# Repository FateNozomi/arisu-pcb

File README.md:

# Arisu Keyboard PCB
アリス PCB designed using KiCad. The layout is inspired by Lyn's EM7 and TGR Alice with some modification of my own.

Key differences:
- I removed the extra [B] key on the right half and shifted the [NM,.?] row to the left by 0.25U.
- Shifted the 3 keys to the right and added arrow keys.
- Tweaked the bottom so that the 1.5U keys doesn't protrude out a little.

Shifting the [NM,.?] row to the left by 0.25U required quite some work on the arrangement of keys for the right half.
As a result, this does not give the same typing experience as Lyn's EM7 and TGR Alice.
Lyn's EM7 and TGR Alice uses the home row as the center point to vertically align both halves while I used the number row instead.
Due to the nature of staggered keyboards, aligning using the number row resulted in the home row not being aligned.

Disclaimer: Use these files at your own risk.

## Gerber Files
Download the gerber files under [releases](https://github.com/FateNozomi/arisu-pcb/releases).

## Assembly
For the components required, you may refer to the bill of materials included along with the release as reference or load up the design file in KiCad.
All the components can be soldered using a regular soldering iron, though soldering the Micro USB receptacle might be the biggest hurdle.

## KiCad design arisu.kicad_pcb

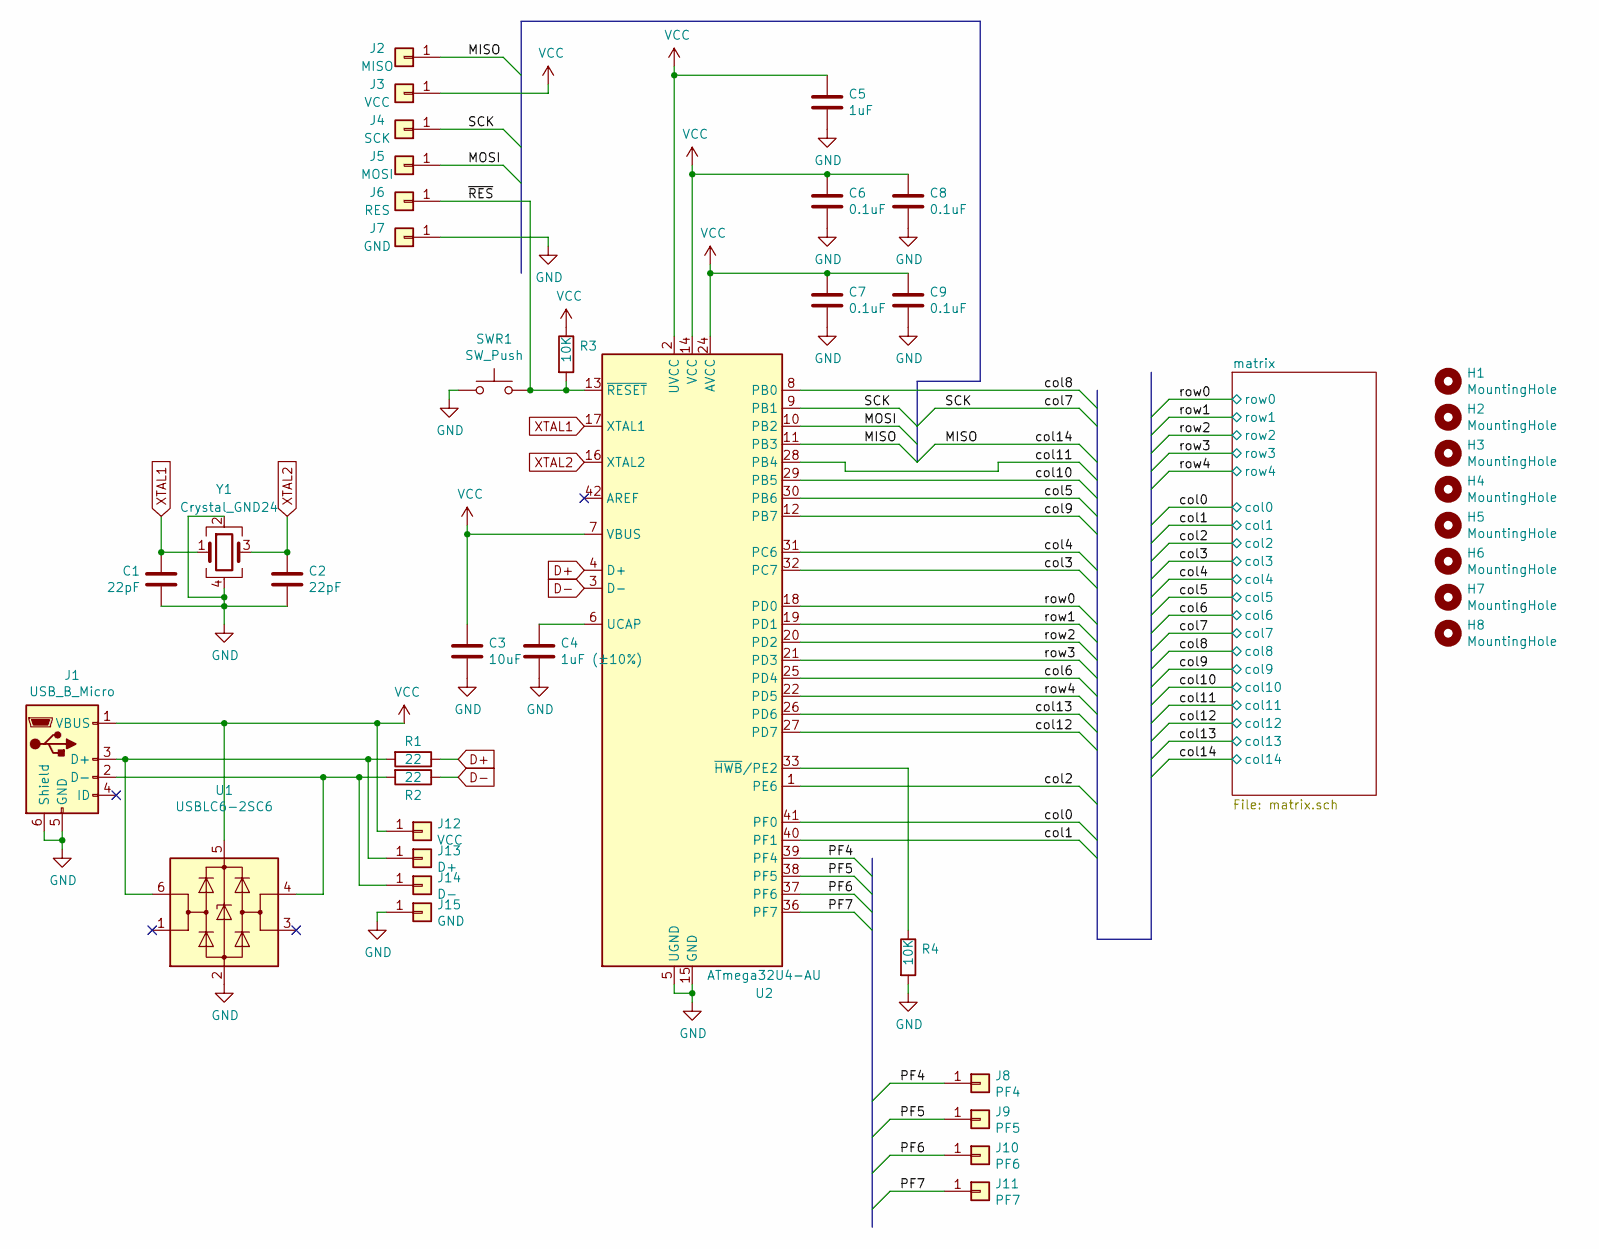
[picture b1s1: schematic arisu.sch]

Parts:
C1, C2: 22pF; C_0805_HandSoldering
C3: 10uF; C_0805_HandSoldering
C4: 1uF (±10%); C_0805_HandSoldering
C5: 1uF; C_0805_HandSoldering
C6, C7, C8, C9: 0.1uF; C_0805_HandSoldering
H1, H2, H3, H4, H5, H6, H7, H8: MountingHole; MountingHole_2.2mm_M2_Pad
J1: USB_B_Micro; USB_Micro-B_Molex-105017-0001
J2: MISO; Pin_Header_Straight_1x01_Pitch2.54mm
J3, J12: VCC; Pin_Header_Straight_1x01_Pitch2.54mm
J4: SCK; Pin_Header_Straight_1x01_Pitch2.54mm
J5: MOSI; Pin_Header_Straight_1x01_Pitch2.54mm
J6: RES; Pin_Header_Straight_1x01_Pitch2.54mm
J7, J15: GND; Pin_Header_Straight_1x01_Pitch2.54mm
J8: PF4; Pin_Header_Straight_1x01_Pitch2.54mm
J9: PF5; Pin_Header_Straight_1x01_Pitch2.54mm
J10: PF6; Pin_Header_Straight_1x01_Pitch2.54mm
J11: PF7; Pin_Header_Straight_1x01_Pitch2.54mm
J13: D+; Pin_Header_Straight_1x01_Pitch2.54mm
J14: D-; Pin_Header_Straight_1x01_Pitch2.54mm
R1, R2: 22; R_0805_HandSoldering
R3, R4: 10K; R_0805_HandSoldering
SWR1: SW_Push; SW_SPST_TL3342
U1: USBLC6-2SC6; SOT-23-6_Handsoldering
U2: ATmega32U4-AU; TQFP-44_10x10mm_Pitch0.8mm
Y1: Crystal_GND24; Crystal_SMD_SeikoEpson_FA238-4pin_3.2x2.5mm_HandSoldering

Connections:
/MISO: J2.1, U2.11 (PB3); also elsewhere on the board
/MOSI: J5.1, U2.10 (PB2); also elsewhere on the board
/PF4: J8.1, U2.39 (PF4); also elsewhere on the board
/PF5: J9.1, U2.38 (PF5); also elsewhere on the board
/PF6: J10.1, U2.37 (PF6); also elsewhere on the board
/PF7: J11.1, U2.36 (PF7); also elsewhere on the board
/SCK: J4.1, U2.9 (PB1); also elsewhere on the board
/col0: U2.41 (PF0); also elsewhere on the board
/col1: U2.40 (PF1); also elsewhere on the board
/col2: U2.1 (PE6); also elsewhere on the board
/col3: U2.32 (PC7); also elsewhere on the board
/col4: U2.31 (PC6); also elsewhere on the board
/col5: U2.30 (PB6); also elsewhere on the board
/col6: U2.25 (PD4); also elsewhere on the board
/col8: U2.8 (PB0); also elsewhere on the board
/col9: U2.12 (PB7); also elsewhere on the board
/col10: U2.29 (PB5); also elsewhere on the board
/col11: U2.28 (PB4); also elsewhere on the board
/col12: U2.27 (PD7); also elsewhere on the board
/col13: U2.26 (PD6); also elsewhere on the board
/row0: U2.18 (PD0); also elsewhere on the board
/row1: U2.19 (PD1); also elsewhere on the board
/row2: U2.20 (PD2); also elsewhere on the board
/row3: U2.21 (PD3); also elsewhere on the board
/row4: U2.22 (PD5); also elsewhere on the board
/~RES~: J6.1, R3.2, SWR1.2, U2.13 (~RESET); also elsewhere on the board
D+: R1.1, U2.4 (D+)
D-: R2.1, U2.3 (D-)
GND: C1.1, C2.2, C3.2, C4.2, C5.2, C6.2, C7.2, C8.2, C9.2, J1.5 (GND), J1.6 (Shield), J7.1, J15.1, R4.2, SWR1.1, U1.2 (GND), U2.5 (UGND), U2.15 (GND), U2.23 (GND), U2.35 (GND), U2.43 (GND), Y1.2, Y1.4; also elsewhere on the board
unnamed: C4.1, U2.6 (UCAP)
unnamed 97: J1.2 (D-), J14.1, R2.2, U1.4 (I/O2); also elsewhere on the board
unnamed 98: J1.3 (D+), J13.1, R1.2, U1.6 (I/O1); also elsewhere on the board
unnamed: R4.1, U2.33 (~HWB~/PE2)
VCC: C3.1, C5.1, C6.1, C7.1, C8.1, C9.1, J1.1 (VBUS), J3.1, J12.1, R3.1, U1.5 (VBUS), U2.2 (UVCC), U2.7 (VBUS), U2.14 (VCC), U2.24 (AVCC), U2.34 (VCC), U2.44 (AVCC); also elsewhere on the board
XTAL1: C1.2, U2.17 (XTAL1), Y1.1
XTAL2: C2.1, U2.16 (XTAL2), Y1.3

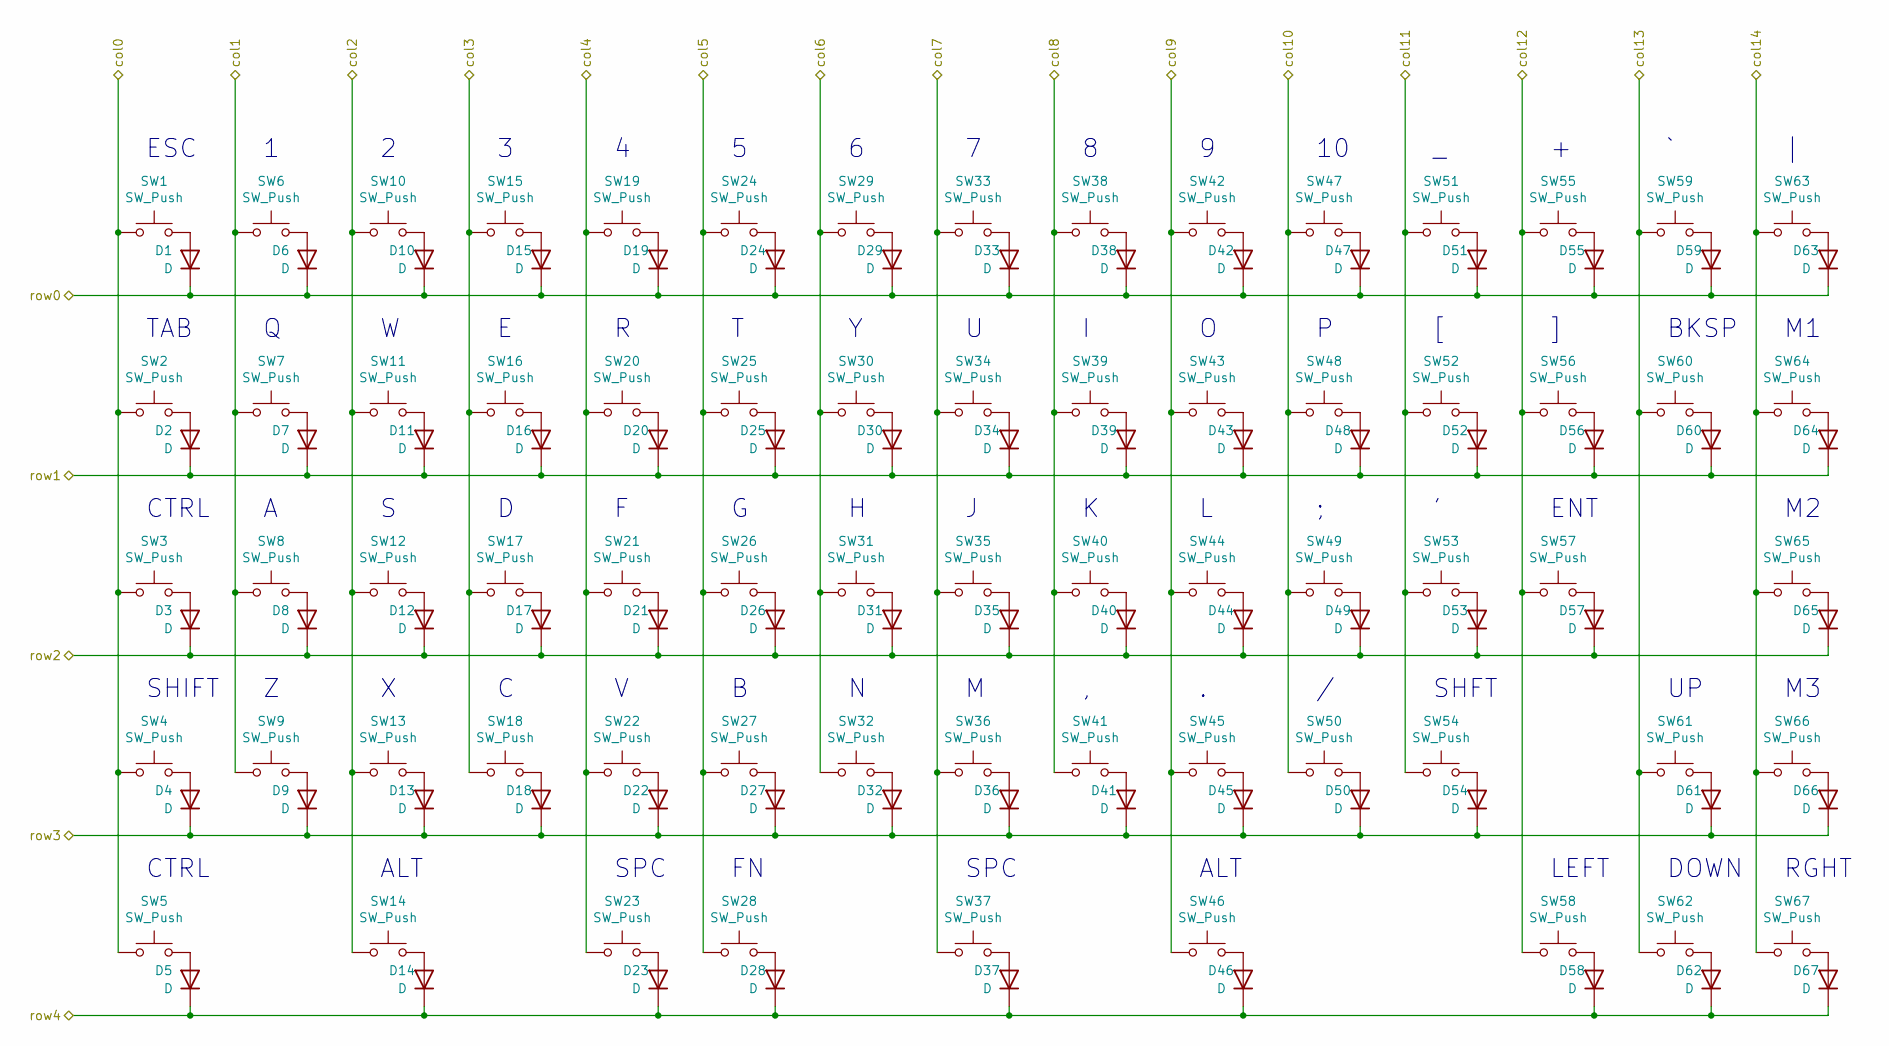
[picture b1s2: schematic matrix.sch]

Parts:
D1, D2, D3, D4, D5, D6, D7, D8, D9, D10, D11, D12, D13, D14, D15, D16, D17, D18, D19, D20, D21, D22, D23, D24, D25, D26, D27, D28, D29, D30, D31, D32, D33, D34, D35, D36, D37, D38, D39, D40, D41, D42, D43, D44, D45, D46, D47, D48, D49, D50, D51, D52, D53, D54, D55, D56, D57, D58, D59, D60, D61, D62, D63, D64, D65, D66, D67: D; D_SOD-123
SW1, SW6, SW7, SW8, SW9, SW10, SW11, SW12, SW13, SW15, SW16, SW17, SW18, SW19, SW20, SW21, SW22, SW24, SW25, SW26, SW27, SW28, SW29, SW30, SW31, SW32, SW33, SW34, SW35, SW36, SW38, SW39, SW40, SW41, SW42, SW43, SW44, SW45, SW47, SW48, SW49, SW50, SW51, SW52, SW53, SW55, SW56, SW58, SW59, SW61, SW62, SW63, SW64, SW65, SW66, SW67: SW_Push; SW_Cherry_MX_1.00u_PCB
SW2, SW5, SW14, SW46, SW60: SW_Push; SW_Cherry_MX_1.50u_PCB
SW3, SW54: SW_Push; SW_Cherry_MX_1.75u_PCB
SW4: SW_Push; SW_Cherry_MX_2.25u_PCB
SW23: SW_Push; SW_Cherry_MX_2.00u_PCB_ReversedStabilizers
SW37: SW_Push; SW_Cherry_MX_2.75u_PCB_ReversedStabilizers
SW57: SW_Push; SW_Cherry_MX_2.25u_PCB_ReversedStabilizers

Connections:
/MISO: SW63.1, SW64.1, SW65.1, SW66.1, SW67.1; also elsewhere on the board
/SCK: SW33.1, SW34.1, SW35.1, SW36.1, SW37.1; also elsewhere on the board
/col0: SW1.1, SW2.1, SW3.1, SW4.1, SW5.1; also elsewhere on the board
/col1: SW6.1, SW7.1, SW8.1, SW9.1; also elsewhere on the board
/col2: SW10.1, SW11.1, SW12.1, SW13.1, SW14.1; also elsewhere on the board
/col3: SW15.1, SW16.1, SW17.1, SW18.1; also elsewhere on the board
/col4: SW19.1, SW20.1, SW21.1, SW22.1, SW23.1; also elsewhere on the board
/col5: SW24.1, SW25.1, SW26.1, SW27.1, SW28.1; also elsewhere on the board
/col6: SW29.1, SW30.1, SW31.1, SW32.1; also elsewhere on the board
/col8: SW38.1, SW39.1, SW40.1, SW41.1; also elsewhere on the board
/col9: SW42.1, SW43.1, SW44.1, SW45.1, SW46.1; also elsewhere on the board
/col10: SW47.1, SW48.1, SW49.1, SW50.1; also elsewhere on the board
/col11: SW51.1, SW52.1, SW53.1, SW54.1; also elsewhere on the board
/col12: SW55.1, SW56.1, SW57.1, SW58.1; also elsewhere on the board
/col13: SW59.1, SW60.1, SW61.1, SW62.1; also elsewhere on the board
/row0: D1.1 (K), D6.1 (K), D10.1 (K), D15.1 (K), D19.1 (K), D24.1 (K), D29.1 (K), D33.1 (K), D38.1 (K), D42.1 (K), D47.1 (K), D51.1 (K), D55.1 (K), D59.1 (K), D63.1 (K); also elsewhere on the board
/row1: D2.1 (K), D7.1 (K), D11.1 (K), D16.1 (K), D20.1 (K), D25.1 (K), D30.1 (K), D34.1 (K), D39.1 (K), D43.1 (K), D48.1 (K), D52.1 (K), D56.1 (K), D60.1 (K), D64.1 (K); also elsewhere on the board
/row2: D3.1 (K), D8.1 (K), D12.1 (K), D17.1 (K), D21.1 (K), D26.1 (K), D31.1 (K), D35.1 (K), D40.1 (K), D44.1 (K), D49.1 (K), D53.1 (K), D57.1 (K), D65.1 (K); also elsewhere on the board
/row3: D4.1 (K), D9.1 (K), D13.1 (K), D18.1 (K), D22.1 (K), D27.1 (K), D32.1 (K), D36.1 (K), D41.1 (K), D45.1 (K), D50.1 (K), D54.1 (K), D61.1 (K), D66.1 (K); also elsewhere on the board
/row4: D5.1 (K), D14.1 (K), D23.1 (K), D28.1 (K), D37.1 (K), D46.1 (K), D58.1 (K), D62.1 (K), D67.1 (K); also elsewhere on the board
unnamed: D1.2 (A), SW1.2
unnamed: D2.2 (A), SW2.2
unnamed: D3.2 (A), SW3.2
unnamed: D4.2 (A), SW4.2
unnamed: D5.2 (A), SW5.2
unnamed: D6.2 (A), SW6.2
unnamed: D7.2 (A), SW7.2
unnamed: D8.2 (A), SW8.2
unnamed: D9.2 (A), SW9.2
unnamed: D10.2 (A), SW10.2
unnamed: D11.2 (A), SW11.2
unnamed: D12.2 (A), SW12.2
unnamed: D13.2 (A), SW13.2
unnamed: D14.2 (A), SW14.2
unnamed: D15.2 (A), SW15.2
unnamed: D16.2 (A), SW16.2
unnamed: D17.2 (A), SW17.2
unnamed: D18.2 (A), SW18.2
unnamed: D19.2 (A), SW19.2
unnamed: D20.2 (A), SW20.2
unnamed: D21.2 (A), SW21.2
unnamed: D22.2 (A), SW22.2
unnamed: D23.2 (A), SW23.2
unnamed: D24.2 (A), SW24.2
unnamed: D25.2 (A), SW25.2
unnamed: D26.2 (A), SW26.2
unnamed: D27.2 (A), SW27.2
unnamed: D28.2 (A), SW28.2
unnamed: D29.2 (A), SW29.2
unnamed: D30.2 (A), SW30.2
unnamed: D31.2 (A), SW31.2
unnamed: D32.2 (A), SW32.2
unnamed: D33.2 (A), SW33.2
unnamed: D34.2 (A), SW34.2
unnamed: D35.2 (A), SW35.2
unnamed: D36.2 (A), SW36.2
unnamed: D37.2 (A), SW37.2
unnamed: D38.2 (A), SW38.2
unnamed: D39.2 (A), SW39.2
unnamed: D40.2 (A), SW40.2
unnamed: D41.2 (A), SW41.2
unnamed: D42.2 (A), SW42.2
unnamed: D43.2 (A), SW43.2
unnamed: D44.2 (A), SW44.2
unnamed: D45.2 (A), SW45.2
unnamed: D46.2 (A), SW46.2
unnamed: D47.2 (A), SW47.2
unnamed: D48.2 (A), SW48.2
unnamed: D49.2 (A), SW49.2
unnamed: D50.2 (A), SW50.2
unnamed: D51.2 (A), SW51.2
unnamed: D52.2 (A), SW52.2
unnamed: D53.2 (A), SW53.2
unnamed: D54.2 (A), SW54.2
unnamed: D55.2 (A), SW55.2
unnamed: D56.2 (A), SW56.2
unnamed: D57.2 (A), SW57.2
unnamed: D58.2 (A), SW58.2
unnamed: D59.2 (A), SW59.2
unnamed: D60.2 (A), SW60.2
unnamed: D61.2 (A), SW61.2
unnamed: D62.2 (A), SW62.2
unnamed: D63.2 (A), SW63.2
unnamed: D64.2 (A), SW64.2
unnamed: D65.2 (A), SW65.2
unnamed: D66.2 (A), SW66.2
unnamed: D67.2 (A), SW67.2

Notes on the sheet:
ESC
TAB
BKSP
CTRL
ENT
SHIFT
SHFT
ALT
SPC
DOWN
LEFT
RGHT

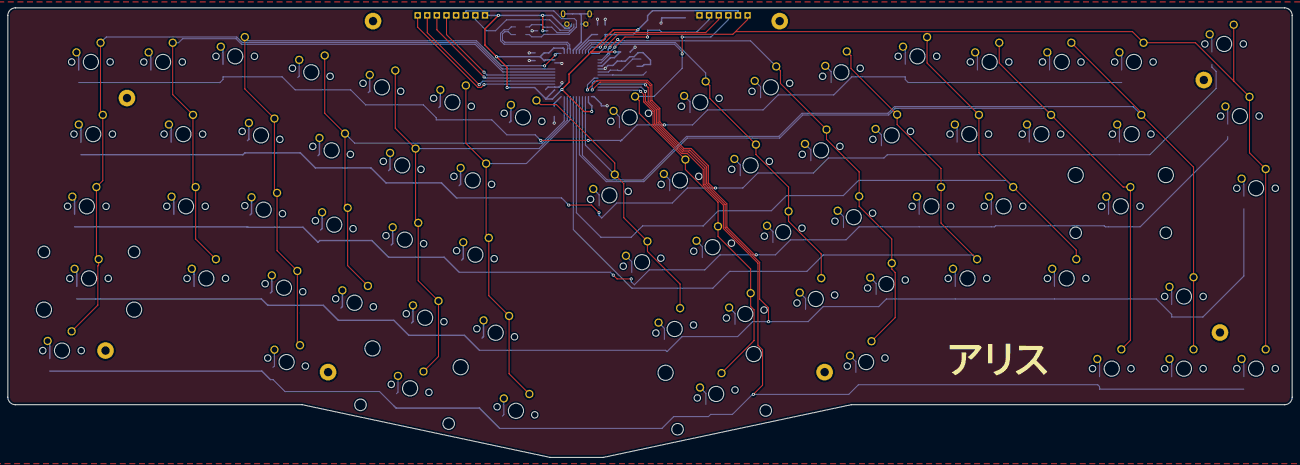
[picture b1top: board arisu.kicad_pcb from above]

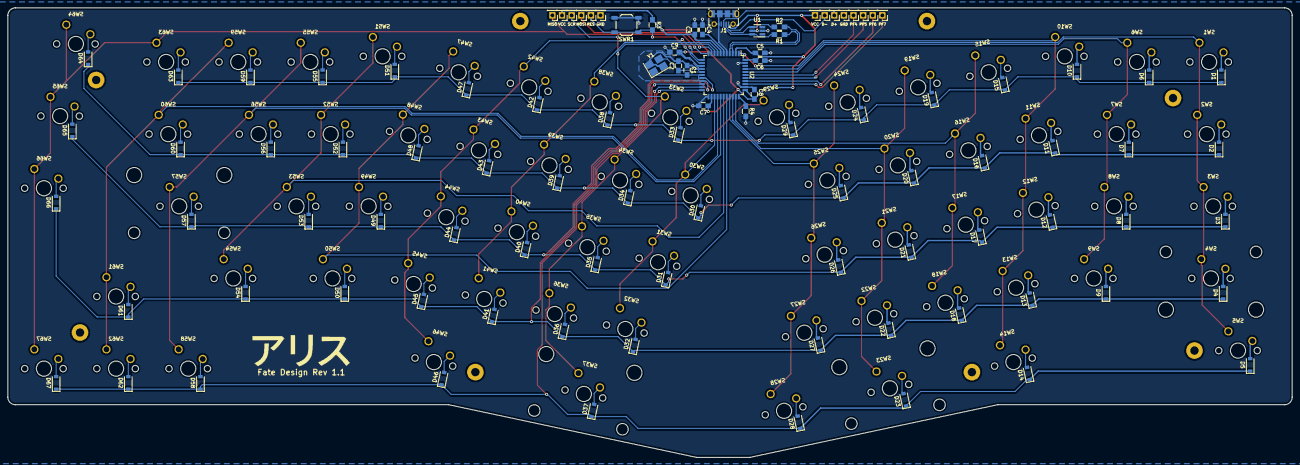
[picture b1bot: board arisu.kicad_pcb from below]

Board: 2 copper layers, 339.1 x 118.7 mm, 174 parts (99 on the bottom side), 103 nets.

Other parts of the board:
D+: D+; Pin_Header_Straight_1x01_Pitch2.54mm
D-: D-; Pin_Header_Straight_1x01_Pitch2.54mm
GND: GND; Pin_Header_Straight_1x01_Pitch2.54mm
GND#2: GND; Pin_Header_Straight_1x01_Pitch2.54mm
MISO: MISO; Pin_Header_Straight_1x01_Pitch2.54mm
MOSI: MOSI; Pin_Header_Straight_1x01_Pitch2.54mm
PF4: PF4; Pin_Header_Straight_1x01_Pitch2.54mm
PF5: PF5; Pin_Header_Straight_1x01_Pitch2.54mm
PF6: PF6; Pin_Header_Straight_1x01_Pitch2.54mm
PF7: PF7; Pin_Header_Straight_1x01_Pitch2.54mm
RES: RES; Pin_Header_Straight_1x01_Pitch2.54mm
SCK: SCK; Pin_Header_Straight_1x01_Pitch2.54mm
VCC: VCC; Pin_Header_Straight_1x01_Pitch2.54mm
VCC#2: VCC; Pin_Header_Straight_1x01_Pitch2.54mm

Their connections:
/MISO: MISO.1; also elsewhere on the board
/MOSI: MOSI.1; also elsewhere on the board
/PF4: PF4.1; also elsewhere on the board
/PF5: PF5.1; also elsewhere on the board
/PF6: PF6.1; also elsewhere on the board
/PF7: PF7.1; also elsewhere on the board
/SCK: SCK.1; also elsewhere on the board
/~RES~: RES.1; also elsewhere on the board
GND: GND.1, GND#2.1; also elsewhere on the board
unnamed 97: D-.1; also elsewhere on the board
unnamed 98: D+.1; also elsewhere on the board
VCC: VCC.1, VCC#2.1; also elsewhere on the board

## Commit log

2019-01-26 Assign PCB footprints to schematic symbols
2019-01-27 Update ATMEGA32U4-AU and USBLC6-2SC6 footprints
2019-01-27 Arrange switches and diodes in PCBNEW
2019-01-27 Add diode_position.txt
2019-01-28 Draw Edge.Cuts
2019-01-28 Arrange core components
2019-01-28 Add D+/D- pin header to Pcbnew
2019-01-28 Add D+/D- pin header to schematic
2019-01-28 Define Design Rules
2019-01-28 Route differential pair D+/D- pins to MCU
2019-01-29 Route all components
2019-01-30 Optimize crystal placement
2019-02-03 Optimize ground plane
2019-02-03 Arrange silk screen components
2019-02-03 Add Arisu Logo
2019-02-04 Add mounting holes in schematic
2019-02-04 Add mounting holes in PCBNew
2019-02-09 Plot gerber files for production
2019-07-13 Include fp-info-cache to .gitignore
2019-07-13 Hide mounting hole label H1 on silk screen layer
2019-07-13 Increase D+ and D- differential pair track width
2019-07-13 Add ground fill zone on B.Cu
2019-07-25 Create LICENSE
2020-10-20 Update .gitignore to include *.sch-bak
2020-10-20 Update symbol library to 5.1.7 USB_B_Micro USBLC6-25C6 ATmega32U4-AU
2020-10-20 Update MX_Switch footprints from Fate_Parts
